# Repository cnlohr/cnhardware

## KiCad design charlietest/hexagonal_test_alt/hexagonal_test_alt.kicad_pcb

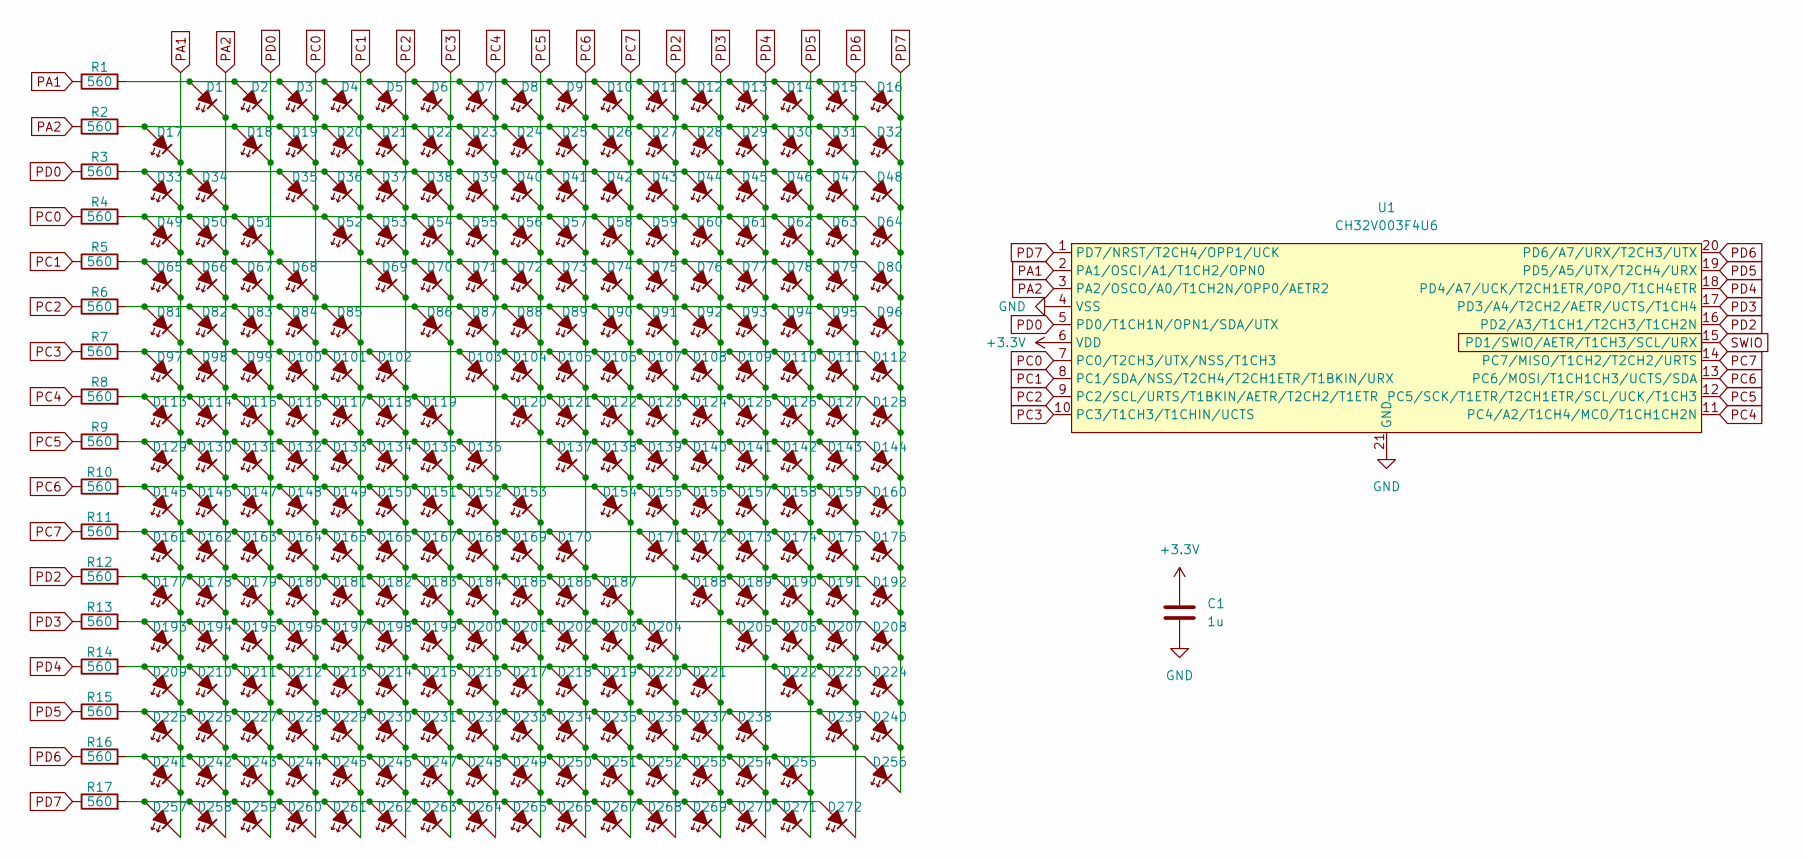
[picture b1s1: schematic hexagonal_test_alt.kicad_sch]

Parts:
C1: 1u; LCSC C52923
D1, D2, D3, D4, D5, D6, D7, D8, D9, D10, D11, D12, D13, D14, D15, D16, D17, D18, D19, D20, D21, D22, D23, D24, D25, D26, D27, D28, D29, D30, D31, D32, D33, D34, D35, D36, D37, D38, D39, D40, D41, D42, D43, D44, D45, D46, D47, D48, D49, D50, D51, D52, D53, D54, D55, D56, D57, D58, D59, D60, D61, D62, D63, D64, D65, D66, D67, D68, D69, D70, D71, D72, D73, D74, D75, D76, D77, D78, D79, D80, D81, D82, D83, D84, D85, D86, D87, D88, D89, D90, D91, D92, D93, D94, D95, D96, D97, D98, D99, D100, D101, D102, D103, D104, D105, D106, D107, D108, D109, D110, D111, D112, D113, D114, D115, D116, D117, D118, D119, D120, D121, D122, D123, D124, D125, D126, D127, D128, D129, D130, D131, D132, D133, D134, D135, D136, D137, D138, D139, D140, D141, D142, D143, D144, D145, D146, D147, D148, D149, D150, D151, D152, D153, D154, D155, D156, D157, D158, D159, D160, D161, D162, D163, D164, D165, D166, D167, D168, D169, D170, D171, D172, D173, D174, D175, D176, D177, D178, D179, D180, D181, D182, D183, D184, D185, D186, D187, D188, D189, D190, D191, D192, D193, D194, D195, D196, D197, D198, D199, D200, D201, D202, D203, D204, D205, D206, D207, D208, D209, D210, D211, D212, D213, D214, D215, D216, D217, D218, D219, D220, D221, D222, D223, D224, D225, D226, D227, D228, D229, D230, D231, D232, D233, D234, D235, D236, D237, D238, D239, D240, D241, D242, D243, D244, D245, D246, D247, D248, D249, D250, D251, D252, D253, D254, D255, D256, D257, D258, D259, D260, D261, D262, D263, D264, D265, D266, D267, D268, D269, D270, D271, D272: LED_45deg_Filled; LED_0603_1608Metric; LCSC C2290
R1, R2, R3, R4, R5, R6, R7, R8, R9, R10, R11, R12, R13, R14, R15, R16, R17: 560; R_0402_1005Metric_COMPACT; LCSC C17798
U1: CH32V003F4U6; QFN-20-1EP_3x3mm_P0.4mm_EP1.65x1.65mm; LCSC C5299908

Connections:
+3.3V: C1.1, U1.6 (VDD)
GND: C1.2, U1.4 (VSS), U1.21 (GND)
unnamed: D1.2 (A), D2.2 (A), D3.2 (A), D4.2 (A), D5.2 (A), D6.2 (A), D7.2 (A), D8.2 (A), D9.2 (A), D10.2 (A), D11.2 (A), D12.2 (A), D13.2 (A), D14.2 (A), D15.2 (A), D16.2 (A), R1.2
unnamed: D17.2 (A), D18.2 (A), D19.2 (A), D20.2 (A), D21.2 (A), D22.2 (A), D23.2 (A), D24.2 (A), D25.2 (A), D26.2 (A), D27.2 (A), D28.2 (A), D29.2 (A), D30.2 (A), D31.2 (A), D32.2 (A), R2.2
unnamed: D33.2 (A), D34.2 (A), D35.2 (A), D36.2 (A), D37.2 (A), D38.2 (A), D39.2 (A), D40.2 (A), D41.2 (A), D42.2 (A), D43.2 (A), D44.2 (A), D45.2 (A), D46.2 (A), D47.2 (A), D48.2 (A), R3.2
unnamed: D49.2 (A), D50.2 (A), D51.2 (A), D52.2 (A), D53.2 (A), D54.2 (A), D55.2 (A), D56.2 (A), D57.2 (A), D58.2 (A), D59.2 (A), D60.2 (A), D61.2 (A), D62.2 (A), D63.2 (A), D64.2 (A), R4.2
unnamed: D65.2 (A), D66.2 (A), D67.2 (A), D68.2 (A), D69.2 (A), D70.2 (A), D71.2 (A), D72.2 (A), D73.2 (A), D74.2 (A), D75.2 (A), D76.2 (A), D77.2 (A), D78.2 (A), D79.2 (A), D80.2 (A), R5.2
unnamed: D81.2 (A), D82.2 (A), D83.2 (A), D84.2 (A), D85.2 (A), D86.2 (A), D87.2 (A), D88.2 (A), D89.2 (A), D90.2 (A), D91.2 (A), D92.2 (A), D93.2 (A), D94.2 (A), D95.2 (A), D96.2 (A), R6.2
unnamed: D97.2 (A), D98.2 (A), D99.2 (A), D100.2 (A), D101.2 (A), D102.2 (A), D103.2 (A), D104.2 (A), D105.2 (A), D106.2 (A), D107.2 (A), D108.2 (A), D109.2 (A), D110.2 (A), D111.2 (A), D112.2 (A), R7.2
unnamed: D113.2 (A), D114.2 (A), D115.2 (A), D116.2 (A), D117.2 (A), D118.2 (A), D119.2 (A), D120.2 (A), D121.2 (A), D122.2 (A), D123.2 (A), D124.2 (A), D125.2 (A), D126.2 (A), D127.2 (A), D128.2 (A), R8.2
unnamed: D129.2 (A), D130.2 (A), D131.2 (A), D132.2 (A), D133.2 (A), D134.2 (A), D135.2 (A), D136.2 (A), D137.2 (A), D138.2 (A), D139.2 (A), D140.2 (A), D141.2 (A), D142.2 (A), D143.2 (A), D144.2 (A), R9.2
unnamed: D145.2 (A), D146.2 (A), D147.2 (A), D148.2 (A), D149.2 (A), D150.2 (A), D151.2 (A), D152.2 (A), D153.2 (A), D154.2 (A), D155.2 (A), D156.2 (A), D157.2 (A), D158.2 (A), D159.2 (A), D160.2 (A), R10.2
unnamed: D161.2 (A), D162.2 (A), D163.2 (A), D164.2 (A), D165.2 (A), D166.2 (A), D167.2 (A), D168.2 (A), D169.2 (A), D170.2 (A), D171.2 (A), D172.2 (A), D173.2 (A), D174.2 (A), D175.2 (A), D176.2 (A), R11.2
unnamed: D177.2 (A), D178.2 (A), D179.2 (A), D180.2 (A), D181.2 (A), D182.2 (A), D183.2 (A), D184.2 (A), D185.2 (A), D186.2 (A), D187.2 (A), D188.2 (A), D189.2 (A), D190.2 (A), D191.2 (A), D192.2 (A), R12.2
unnamed: D193.2 (A), D194.2 (A), D195.2 (A), D196.2 (A), D197.2 (A), D198.2 (A), D199.2 (A), D200.2 (A), D201.2 (A), D202.2 (A), D203.2 (A), D204.2 (A), D205.2 (A), D206.2 (A), D207.2 (A), D208.2 (A), R13.2
unnamed: D209.2 (A), D210.2 (A), D211.2 (A), D212.2 (A), D213.2 (A), D214.2 (A), D215.2 (A), D216.2 (A), D217.2 (A), D218.2 (A), D219.2 (A), D220.2 (A), D221.2 (A), D222.2 (A), D223.2 (A), D224.2 (A), R14.2
unnamed: D225.2 (A), D226.2 (A), D227.2 (A), D228.2 (A), D229.2 (A), D230.2 (A), D231.2 (A), D232.2 (A), D233.2 (A), D234.2 (A), D235.2 (A), D236.2 (A), D237.2 (A), D238.2 (A), D239.2 (A), D240.2 (A), R15.2
unnamed: D241.2 (A), D242.2 (A), D243.2 (A), D244.2 (A), D245.2 (A), D246.2 (A), D247.2 (A), D248.2 (A), D249.2 (A), D250.2 (A), D251.2 (A), D252.2 (A), D253.2 (A), D254.2 (A), D255.2 (A), D256.2 (A), R16.2
unnamed: D257.2 (A), D258.2 (A), D259.2 (A), D260.2 (A), D261.2 (A), D262.2 (A), D263.2 (A), D264.2 (A), D265.2 (A), D266.2 (A), D267.2 (A), D268.2 (A), D269.2 (A), D270.2 (A), D271.2 (A), D272.2 (A), R17.2
PA1: D17.1 (K), D33.1 (K), D49.1 (K), D65.1 (K), D81.1 (K), D97.1 (K), D113.1 (K), D129.1 (K), D145.1 (K), D161.1 (K), D177.1 (K), D193.1 (K), D209.1 (K), D225.1 (K), D241.1 (K), D257.1 (K), R1.1, U1.2 (PA1/OSCI/A1/T1CH2/OPN0)
PA2: D1.1 (K), D34.1 (K), D50.1 (K), D66.1 (K), D82.1 (K), D98.1 (K), D114.1 (K), D130.1 (K), D146.1 (K), D162.1 (K), D178.1 (K), D194.1 (K), D210.1 (K), D226.1 (K), D242.1 (K), D258.1 (K), R2.1, U1.3 (PA2/OSCO/A0/T1CH2N/OPP0/AETR2)
PC0: D3.1 (K), D19.1 (K), D35.1 (K), D68.1 (K), D84.1 (K), D100.1 (K), D116.1 (K), D132.1 (K), D148.1 (K), D164.1 (K), D180.1 (K), D196.1 (K), D212.1 (K), D228.1 (K), D244.1 (K), D260.1 (K), R4.1, U1.7 (PC0/T2CH3/UTX/NSS/T1CH3)
PC1: D4.1 (K), D20.1 (K), D36.1 (K), D52.1 (K), D85.1 (K), D101.1 (K), D117.1 (K), D133.1 (K), D149.1 (K), D165.1 (K), D181.1 (K), D197.1 (K), D213.1 (K), D229.1 (K), D245.1 (K), D261.1 (K), R5.1, U1.8 (PC1/SDA/NSS/T2CH4/T2CH1ETR/T1BKIN/URX)
PC2: D5.1 (K), D21.1 (K), D37.1 (K), D53.1 (K), D69.1 (K), D102.1 (K), D118.1 (K), D134.1 (K), D150.1 (K), D166.1 (K), D182.1 (K), D198.1 (K), D214.1 (K), D230.1 (K), D246.1 (K), D262.1 (K), R6.1, U1.9 (PC2/SCL/URTS/T1BKIN/AETR/T2CH2/T1ETR)
PC3: D6.1 (K), D22.1 (K), D38.1 (K), D54.1 (K), D70.1 (K), D86.1 (K), D119.1 (K), D135.1 (K), D151.1 (K), D167.1 (K), D183.1 (K), D199.1 (K), D215.1 (K), D231.1 (K), D247.1 (K), D263.1 (K), R7.1, U1.10 (PC3/T1CH3/T1CHIN/UCTS)
PC4: D7.1 (K), D23.1 (K), D39.1 (K), D55.1 (K), D71.1 (K), D87.1 (K), D103.1 (K), D136.1 (K), D152.1 (K), D168.1 (K), D184.1 (K), D200.1 (K), D216.1 (K), D232.1 (K), D248.1 (K), D264.1 (K), R8.1, U1.11 (PC4/A2/T1CH4/MCO/T1CH1CH2N)
PC5: D8.1 (K), D24.1 (K), D40.1 (K), D56.1 (K), D72.1 (K), D88.1 (K), D104.1 (K), D120.1 (K), D153.1 (K), D169.1 (K), D185.1 (K), D201.1 (K), D217.1 (K), D233.1 (K), D249.1 (K), D265.1 (K), R9.1, U1.12 (PC5/SCK/T1ETR/T2CH1ETR/SCL/UCK/T1CH3)
PC6: D9.1 (K), D25.1 (K), D41.1 (K), D57.1 (K), D73.1 (K), D89.1 (K), D105.1 (K), D121.1 (K), D137.1 (K), D170.1 (K), D186.1 (K), D202.1 (K), D218.1 (K), D234.1 (K), D250.1 (K), D266.1 (K), R10.1, U1.13 (PC6/MOSI/T1CH1CH3/UCTS/SDA)
PC7: D10.1 (K), D26.1 (K), D42.1 (K), D58.1 (K), D74.1 (K), D90.1 (K), D106.1 (K), D122.1 (K), D138.1 (K), D154.1 (K), D187.1 (K), D203.1 (K), D219.1 (K), D235.1 (K), D251.1 (K), D267.1 (K), R11.1, U1.14 (PC7/MISO/T1CH2/T2CH2/URTS)
PD0: D2.1 (K), D18.1 (K), D51.1 (K), D67.1 (K), D83.1 (K), D99.1 (K), D115.1 (K), D131.1 (K), D147.1 (K), D163.1 (K), D179.1 (K), D195.1 (K), D211.1 (K), D227.1 (K), D243.1 (K), D259.1 (K), R3.1, U1.5 (PD0/T1CH1N/OPN1/SDA/UTX)
PD2: D11.1 (K), D27.1 (K), D43.1 (K), D59.1 (K), D75.1 (K), D91.1 (K), D107.1 (K), D123.1 (K), D139.1 (K), D155.1 (K), D171.1 (K), D204.1 (K), D220.1 (K), D236.1 (K), D252.1 (K), D268.1 (K), R12.1, U1.16 (PD2/A3/T1CH1/T2CH3/T1CH2N)
PD3: D12.1 (K), D28.1 (K), D44.1 (K), D60.1 (K), D76.1 (K), D92.1 (K), D108.1 (K), D124.1 (K), D140.1 (K), D156.1 (K), D172.1 (K), D188.1 (K), D221.1 (K), D237.1 (K), D253.1 (K), D269.1 (K), R13.1, U1.17 (PD3/A4/T2CH2/AETR/UCTS/T1CH4)
PD4: D13.1 (K), D29.1 (K), D45.1 (K), D61.1 (K), D77.1 (K), D93.1 (K), D109.1 (K), D125.1 (K), D141.1 (K), D157.1 (K), D173.1 (K), D189.1 (K), D205.1 (K), D238.1 (K), D254.1 (K), D270.1 (K), R14.1, U1.18 (PD4/A7/UCK/T2CH1ETR/OPO/T1CH4ETR)
PD5: D14.1 (K), D30.1 (K), D46.1 (K), D62.1 (K), D78.1 (K), D94.1 (K), D110.1 (K), D126.1 (K), D142.1 (K), D158.1 (K), D174.1 (K), D190.1 (K), D206.1 (K), D222.1 (K), D255.1 (K), D271.1 (K), R15.1, U1.19 (PD5/A5/UTX/T2CH4/URX)
PD6: D15.1 (K), D31.1 (K), D47.1 (K), D63.1 (K), D79.1 (K), D95.1 (K), D111.1 (K), D127.1 (K), D143.1 (K), D159.1 (K), D175.1 (K), D191.1 (K), D207.1 (K), D223.1 (K), D239.1 (K), D272.1 (K), R16.1, U1.20 (PD6/A7/URX/T2CH3/UTX)
PD7: D16.1 (K), D32.1 (K), D48.1 (K), D64.1 (K), D80.1 (K), D96.1 (K), D112.1 (K), D128.1 (K), D144.1 (K), D160.1 (K), D176.1 (K), D192.1 (K), D208.1 (K), D224.1 (K), D240.1 (K), D256.1 (K), R17.1, U1.1 (PD7/NRST/T2CH4/OPP1/UCK)
SWIO: U1.15 (PD1/SWIO/AETR/T1CH3/SCL/URX)

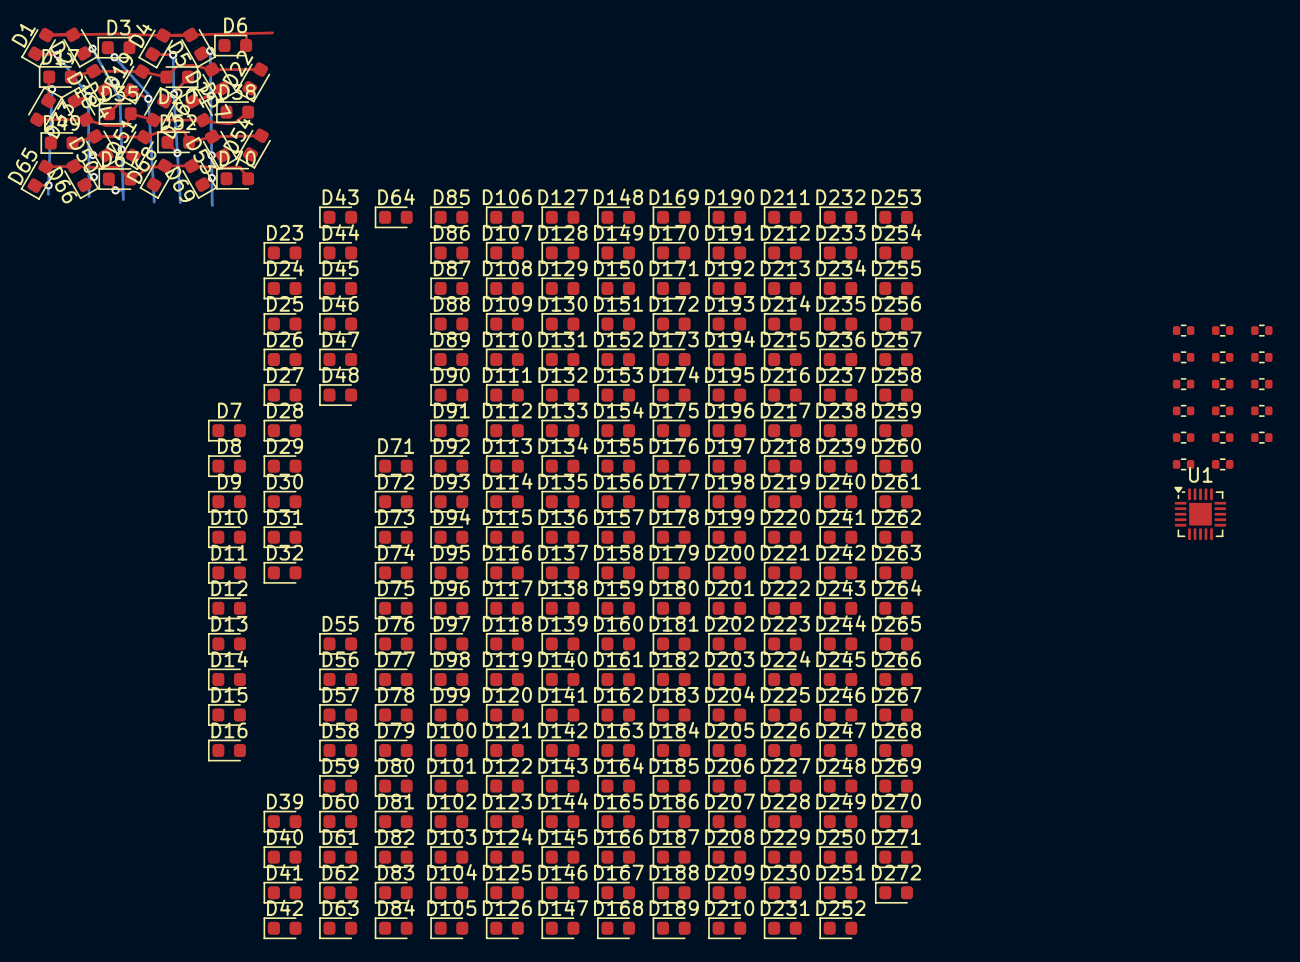
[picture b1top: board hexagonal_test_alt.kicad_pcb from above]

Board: 2 copper layers, 290 parts (0 on the bottom side), 35 nets.

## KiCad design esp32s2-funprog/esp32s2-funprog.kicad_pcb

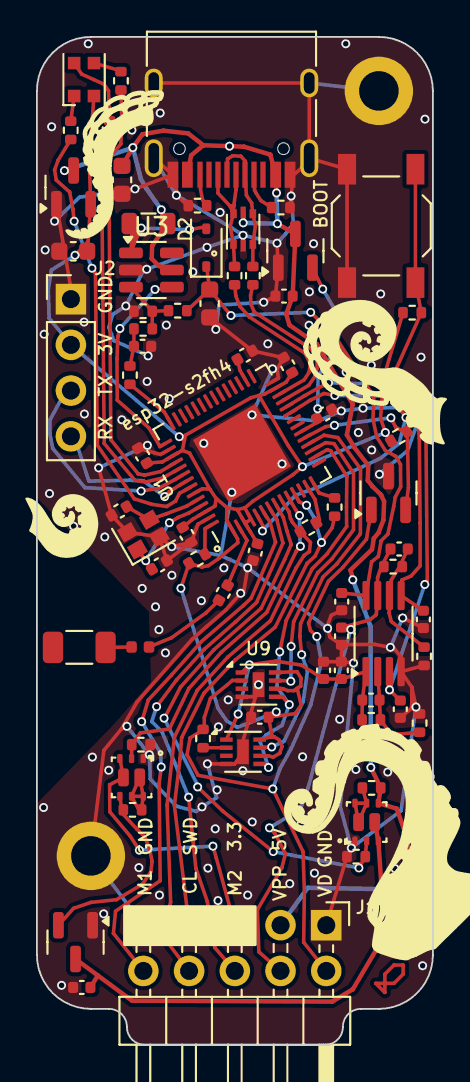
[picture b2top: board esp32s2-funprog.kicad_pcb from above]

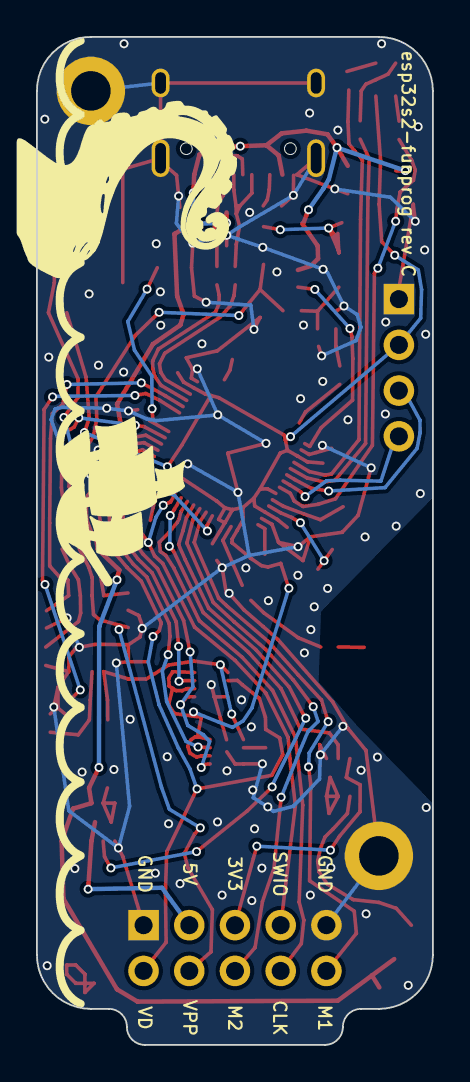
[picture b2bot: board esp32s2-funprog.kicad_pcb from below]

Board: 2 copper layers, 22.0 x 56.0 mm, 79 parts (2 on the bottom side), 57 nets.

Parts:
A1: ANT; R_1206_3216Metric
C1, C14, C15, C17, C21, C23, C24: 10p; C_0402_1005Metric
C2, C3: 2.2p; C_0402_1005Metric
C4, C5, C8, C9, C10, C11, C13, C16, C26: 1u; C_0402_1005Metric
C6, C12, C25: 10u; C_0603_1608Metric
C7, C18, C22: 100n; C_0402_1005Metric
D1: LED_RAGB; LED_WS2812B-2020_PLCC4_2.0x2.0mm
D2: 1N5819WS; D_SOD-323
D4: USBLC6-2P6-TVS; SOT-666
G1: artwork; Tentacle1-Astronautilus
G2: artwork; Tentacle2-Astronautilus
G3: artwork; BoatOnWaterLarge-Astronautilus
G4: artwork; Tentacle4-Astronautilus
G5: artwork; TentacleLargeFlip-Astronautilus
G6: artwork; TentacleLarge-Astronautilus
J1: OPGM; PinHeader_2x05_P2.54mm_Horizontal
J2: PGM; PinHeader_1x04_P2.54mm_Vertical
J3: USB_C_Receptacle_USB2.0; USB_C_Receptacle_HRO_TYPE-C-31-M-12
J4, J5: MOUNT; MountingHole_2.2mm_M2_DIN965_Pad
L1: 6.8nH; L_0402_1005Metric
L2: 4.7u500mA; L_0805_2012Metric
Q1, Q2: SE4625-PandN; DFN-6-2x2-SplitPad
Q4: 2N7002; SOT-23
R1, R2, R3, R4, R7, R8, R30: 10k; R_0402_1005Metric
R5, R6, R11, R12, R20, R22: 5.1k; R_0402_1005Metric
R9, R10: 22; R_0402_1005Metric
R13, R14, R15, R16: 510; R_0402_1005Metric
R17, R18, R24: 2.2k; R_0402_1005Metric
R19, R21: 15k; R_0402_1005Metric
R23: 12k; R_0402_1005Metric
SW1: TS-1187A-B-A-B; SW_SPST_TL3342
U1: ESP32-S2; ESP32S2
U2, U4, U6: XC6206P332; SOT-23
U3: MT3608; SOT-23-6
U5: COSNE5532; MSOP-8_3x3mm_P0.65mm
U9, U14: AT8837; DFN-8-1EP_2x2mm_P0.45mm_EP0.64x1.38mm
Y1: 40MHz; Crystal_SMD_2016-4Pin_2.0x1.6mm

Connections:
3V3SW: J1.5, Q1.3 (D2), Q1.8 (D2)
5VSW: J1.3, Q2.3 (D2), Q2.8 (D2)
+VSW: C7.1, C25.1, D2.1 (K), R23.2, U5.8 (Vcc)
BOOSTEN: U1.43 (MTCK), U3.4 (EN)
BOOSTV: R24.2, U1.42 (GPIO38)
CHIP_PU: R6.1, U1.56 (CHIP_PU)
D+: D4.1 (IO1), D4.6 (IO1), J3.A6 (D+), J3.B6 (D+), R10.2
D-: D4.3 (IO2), D4.4 (IO2), J3.A7 (D-), J3.B7 (D-), R9.1
DAC1: C14.2, U1.23 (DAC1), U5.3 (I1+)
DAC2: C15.2, U1.24 (DAC2), U5.5 (I2+)
GND: C2.1, C3.1, C4.2, C5.2, C6.2, C7.2, C8.2, C9.2, C10.1, C11.2, C12.2, C13.2, C14.1, C15.1, C16.2, C18.2, C22.2, C23.2, C24.2, C25.2, C26.1, D4.2 (GND), J1.1, J1.9, J2.1, J3.A1 (GND), J3.A12 (GND), J3.B1 (GND), J3.B12 (GND), J3.S1 (SHIELD), J4.1, J5.1, Q1.1 (S1), Q2.1 (S1), Q4.3 (S), R3.1, R4.1, R11.2, R12.2, R16.1, R20.1, R22.1, SW1.1 (A), U1.28 (GPIO21), U1.44 (MTDO0), U1.55 (GPIO46), U1.57 (GND), U2.1 (GND), U3.2 (GND), U4.1 (GND), U5.4 (GND), U6.1 (GND), U9.4 (GND), U9.9 (FLAG), U14.4 (GND), U14.9 (FLAG), Y1.2, Y1.4
GPIO0: R5.2, SW1.2 (B), U1.5 (GPIO0)
MULTI1: J1.10, U1.6 (GPIO1)
MULTI2: J1.6, U1.7 (GPIO2)
unnamed: A1.1, L1.1
unnamed: C1.1, L1.2
unnamed: C18.1, R17.1, R24.1
unnamed: D1.4 (BK), R15.2
unnamed: D1.3 (GK), R14.2
unnamed: D1.1 (RK), R13.2
unnamed: D2.2 (A), L2.2, U3.1 (SW)
unnamed: J3.A5 (CC1), R11.1
unnamed: J3.B5 (CC2), R12.1
unnamed: Q1.5 (G2), Q1.6 (D1), Q1.7 (D1), R7.2
unnamed: Q1.4 (S2), R7.1, U6.2 (Q)
unnamed: Q2.5 (G2), Q2.6 (D1), Q2.7 (D1), R8.2
unnamed: R9.2, U1.25 (GPIO19)
unnamed: R10.1, U1.26 (GPIO20)
unnamed: R13.1, U1.50 (GPIO45)
unnamed: C1.2, U1.2 (LNA_IN)
unnamed: R14.1, U1.46 (MTDI)
unnamed: R15.1, U1.47 (MTMS)
unnamed: C4.1, U1.30 (VDD_SPI)
unnamed: C3.2, U1.52 (XTAL_N), Y1.3
unnamed: C2.2, U1.53 (XTAL_P), Y1.1
unnamed: R16.2, R17.2, R23.1, U3.3 (FB)
unnamed: R30.1, U14.2 (OUT1)
OD1: U1.16 (GPIO11), U9.5 (IN2), U14.5 (IN2)
OEN1: U1.17 (GPIO12), U9.7 (nSLP)
OPEN1: U1.18 (GPIO13), U14.7 (nSLP)
RX: J2.4, U1.49 (U0XD)
SWCL: J1.8, R1.1, U1.9 (GPIO4)
SWIO: J1.7, R2.1, U1.11 (GPIO6)
SWPUC: R1.2, U1.13 (GPIO8)
SWPUD: R2.2, U1.14 (GPIO9)
TX: J2.3, U1.48 (U0TXD)
V1FB: C17.2, R19.1, R20.2, U5.2 (I1-)
V2FB: C21.2, R21.1, R22.2, U5.6 (I2-)
VBUS: C10.2, C12.1, C26.2, D4.5 (VB), J3.A4 (VBUS), J3.A9 (VBUS), J3.B4 (VBUS), J3.B9 (VBUS), L2.1, Q2.4 (S2), R8.1, U2.3 (I), U3.5 (IN), U4.3 (I), U6.3 (I)
VCCCTL3: Q1.2 (G1), R3.2, U1.10 (GPIO5)
VCCCTL5: Q2.2 (G1), R4.2, U1.8 (GPIO3)
VD1: C17.1, C22.1, C24.1, R19.2, U5.1 (O1), U9.1 (VM), U14.1 (VM)
VD2: C21.1, C23.1, J1.4, R21.2, U5.7 (O2)
VDD: C5.1, C6.1, C8.1, C9.1, C11.1, C13.1, D1.2 (A), J2.2, R5.1, R6.2, R18.1, U1.1 (VDDA), U1.3 (VDD3P3), U1.4 (VDD3P3), U1.27 (VDD3P3_RTC_IO), U1.45 (VDD3P3_CPU), U1.51 (VDDA), U1.54 (VDDA), U4.2 (Q), U9.6 (IN1), U9.8 (VCC), U14.6 (IN1), U14.8 (VCC)
VDDA: C16.1, U1.20 (V333P3_RTC), U2.2 (Q)
VPI1: Q4.2 (D), R18.2, U1.19 (GPIO14)
VPP1: J1.2, Q4.1 (G), R30.2, U9.2 (OUT1)

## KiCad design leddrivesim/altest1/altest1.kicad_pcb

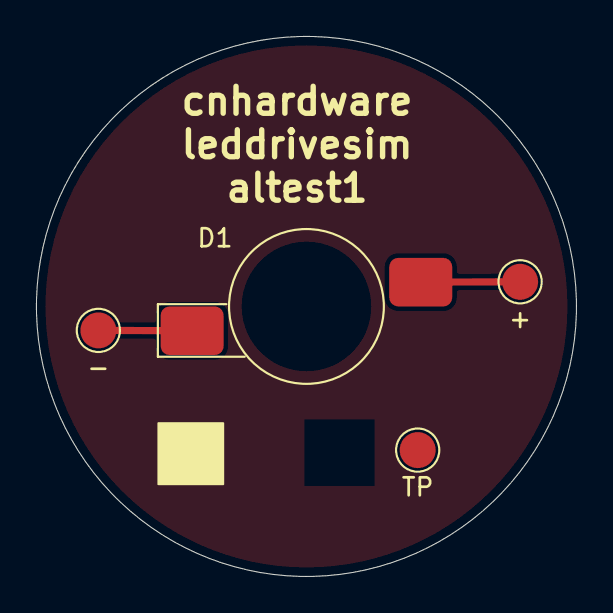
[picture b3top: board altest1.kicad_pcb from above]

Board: 2 copper layers, 30.0 x 30.0 mm, 4 parts (0 on the bottom side), 2 nets.

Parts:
D1: LED_1W_3W; LED_1W_3W_R8-FOR-ALUMINIUM-SUBSTRATE
TP1: +; TestPoint_Pad_D2.0mm
TP2: -; TestPoint_Pad_D2.0mm
TP3: TP; TestPoint_Pad_D2.0mm

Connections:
unnamed: D1.2 (A), TP1.1
unnamed: D1.1 (K), TP2.1

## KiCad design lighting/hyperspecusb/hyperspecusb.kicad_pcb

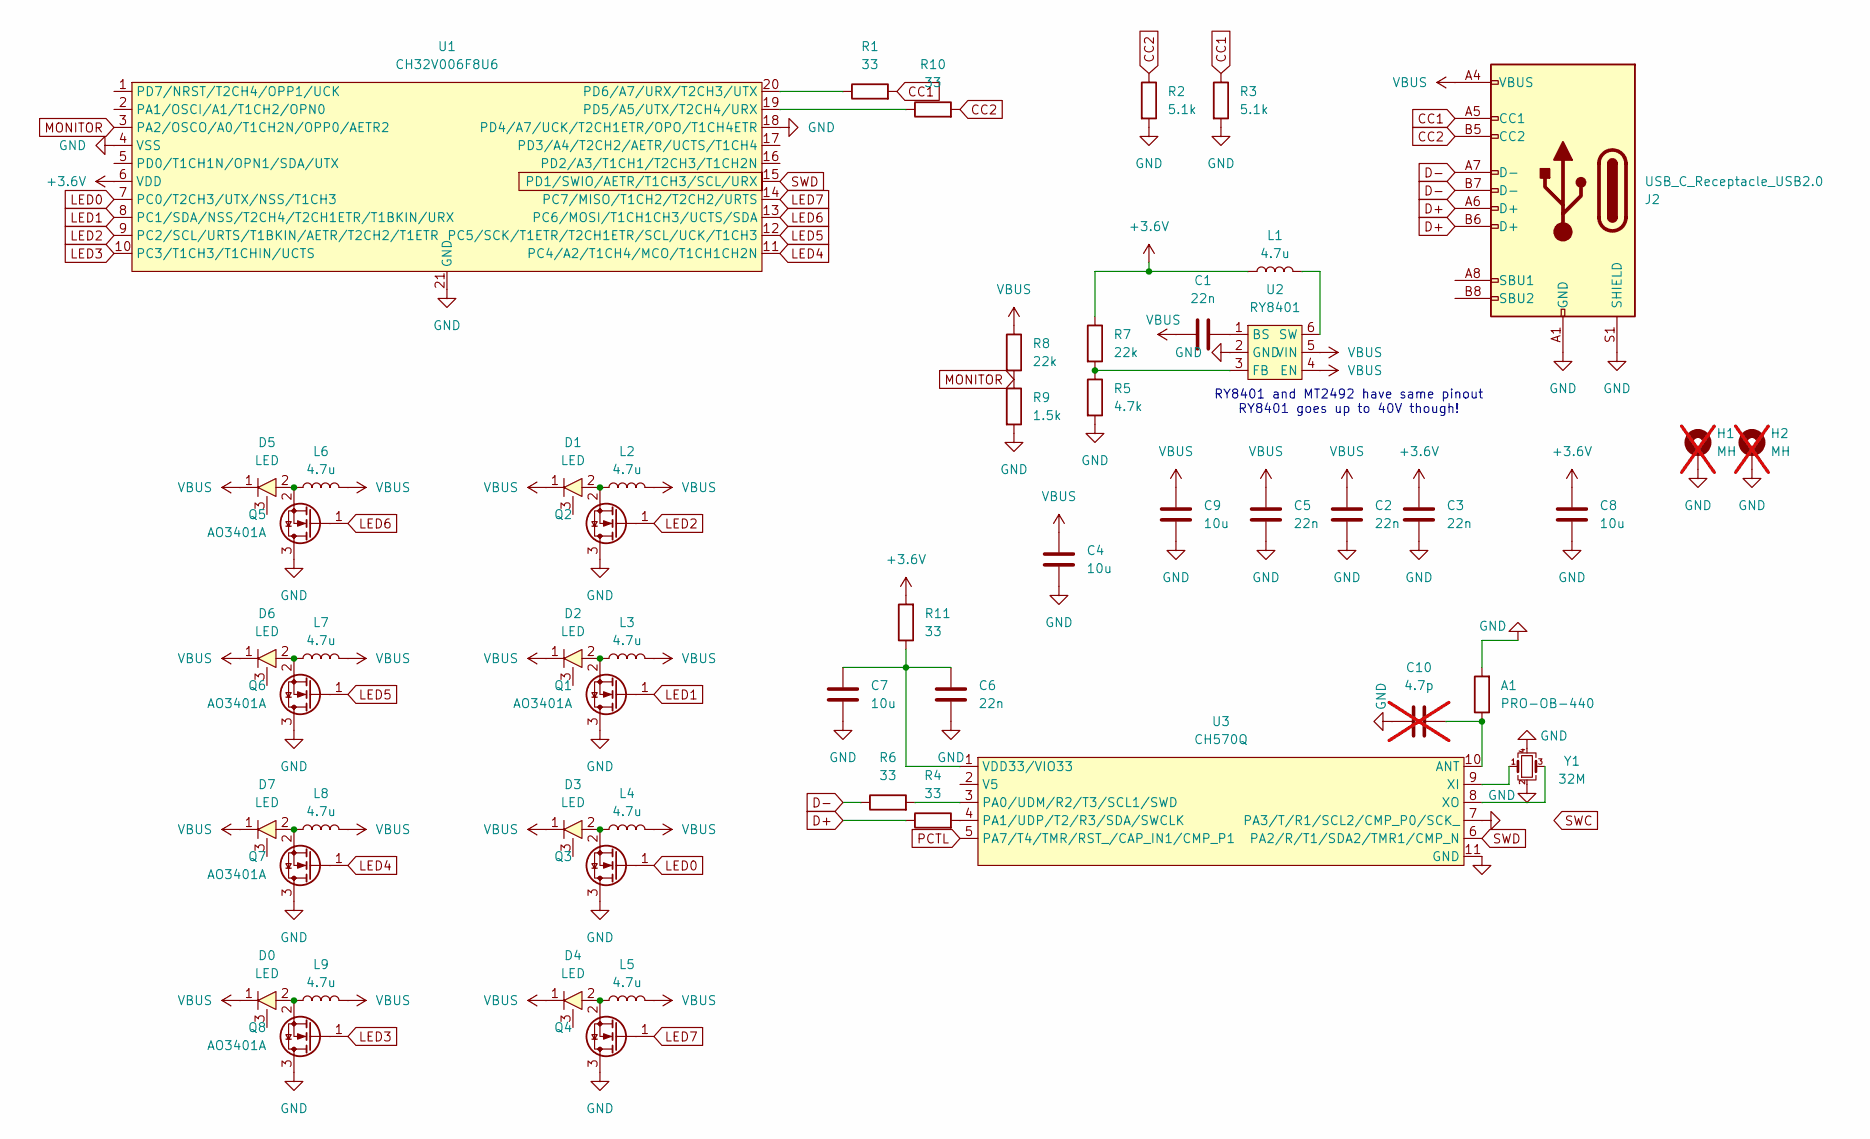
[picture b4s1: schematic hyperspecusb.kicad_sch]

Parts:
A1: PRO-OB-440; Abracon_PRO-OB-440; LCSC C5122736
C1, C2, C3, C5, C6: 22n; C_0402_1005Metric; LCSC C1532
C4, C7, C8, C9: 10u; C_0805_2012Metric; LCSC C15850
C10: 4.7p; C_0402_1005Metric; not fitted
D0, D1, D2, D3, D4, D5, D6, D7: LED; LED_3535_3W_W_PAD
H1, H2: MH; MountingHole_3.2mm_M3_ISO7380_Pad; not fitted
J2: USB_C_Receptacle_USB2.0; USB_C_SMT_ONLY_Receptacle_USB2.0; LCSC C2927040
L1, L2, L3, L4, L5, L6, L7, L8, L9: 4.7u; L_1008_2520Metric; LCSC C88528
Q1, Q2, Q3, Q4, Q5, Q6, Q7, Q8: AO3401A; SOT-23; LCSC C15127
R1, R4, R6, R10, R11: 33; R_0603_1608Metric; LCSC C23140
R2, R3: 5.1k; R_0402_1005Metric; LCSC C25905
R5: 4.7k; R_0402_1005Metric; LCSC C25900
R7, R8: 22k; R_0603_1608Metric; LCSC C31850
R9: 1.5k; R_0402_1005Metric; LCSC C25867
U1: CH32V006F8U6; QFN-20-1EP_3x3mm_P0.4mm_EP1.65x1.65mm; LCSC C42431288
U2: RY8401; SOT-23-6; LCSC C2912960
U3: CH570Q; DFN-10-1EP_3x3mm_P0.5mm_EP1.7x2.5mm; LCSC C49260680
Y1: 32M; Crystal_SMD_2016-4Pin_2.0x1.6mm; LCSC C718072

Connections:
+3.6V: C3.2, C8.2, L1.1, R7.1, R11.2, U1.6 (VDD)
CC1: J2.A5 (CC1), R1.2, R3.1
CC2: J2.B5 (CC2), R2.1, R10.2
D+: J2.A6 (D+), J2.B6 (D+), R4.1
D-: J2.A7 (D-), J2.B7 (D-), R6.1
GND: A1.2, C2.1, C3.1, C4.1, C5.1, C6.1, C7.1, C8.1, C9.1, C10.2, H1.1, H2.1, J2.A1 (GND), J2.A12 (GND), J2.B1 (GND), J2.B12 (GND), J2.S1 (SHIELD), Q1.3 (D), Q2.3 (D), Q3.3 (D), Q4.3 (D), Q5.3 (D), Q6.3 (D), Q7.3 (D), Q8.3 (D), R2.2, R3.2, R5.2, R9.2, U1.4 (VSS), U1.18 (PD4/A7/UCK/T2CH1ETR/OPO/T1CH4ETR), U1.21 (GND), U2.2 (GND), U3.7 (PA3/T/R1/SCL2/CMP_P0/SCK_), U3.11 (GND), Y1.2, Y1.4
LED0: Q3.1 (G), U1.7 (PC0/T2CH3/UTX/NSS/T1CH3)
LED1: Q1.1 (G), U1.8 (PC1/SDA/NSS/T2CH4/T2CH1ETR/T1BKIN/URX)
LED2: Q2.1 (G), U1.9 (PC2/SCL/URTS/T1BKIN/AETR/T2CH2/T1ETR)
LED3: Q8.1 (G), U1.10 (PC3/T1CH3/T1CHIN/UCTS)
LED4: Q7.1 (G), U1.11 (PC4/A2/T1CH4/MCO/T1CH1CH2N)
LED5: Q6.1 (G), U1.12 (PC5/SCK/T1ETR/T2CH1ETR/SCL/UCK/T1CH3)
LED6: Q5.1 (G), U1.13 (PC6/MOSI/T1CH1CH3/UCTS/SDA)
LED7: Q4.1 (G), U1.14 (PC7/MISO/T1CH2/T2CH2/URTS)
MONITOR: R8.2, R9.1, U1.3 (PA2/OSCO/A0/T1CH2N/OPP0/AETR2)
unnamed: D2.2, L3.1, Q1.2 (S)
unnamed: D1.2, L2.1, Q2.2 (S)
unnamed: D3.2, L4.1, Q3.2 (S)
unnamed: D4.2, L5.1, Q4.2 (S)
unnamed: D5.2, L6.1, Q5.2 (S)
unnamed: D6.2, L7.1, Q6.2 (S)
unnamed: D7.2, L8.1, Q7.2 (S)
unnamed: D0.2, L9.1, Q8.2 (S)
unnamed: R10.1, U1.19 (PD5/A5/UTX/T2CH4/URX)
unnamed: R1.1, U1.20 (PD6/A7/URX/T2CH3/UTX)
unnamed: C1.2, U2.1 (BS)
unnamed: R5.1, R7.2, U2.3 (FB)
unnamed: L1.2, U2.6 (SW)
unnamed: A1.1, C10.1, U3.10 (ANT)
unnamed: R6.2, U3.3 (PA0/UDM/R2/T3/SCL1/SWD)
unnamed: R4.2, U3.4 (PA1/UDP/T2/R3/SDA/SWCLK)
unnamed: C6.2, C7.2, R11.1, U3.1 (VDD33/VIO33)
unnamed: U3.9 (XI), Y1.1
unnamed: U3.8 (XO), Y1.3
PCTL: U3.5 (PA7/T4/TMR/RST_/CAP_IN1/CMP_P1)
SWD: U1.15 (PD1/SWIO/AETR/T1CH3/SCL/URX), U3.6 (PA2/R/T1/SDA2/TMR1/CMP_N)
VBUS: C1.1, C2.2, C4.2, C5.2, C9.2, D0.1, D1.1, D2.1, D3.1, D4.1, D5.1, D6.1, D7.1, J2.A4 (VBUS), J2.A9 (VBUS), J2.B4 (VBUS), J2.B9 (VBUS), L2.2, L3.2, L4.2, L5.2, L6.2, L7.2, L8.2, L9.2, R8.1, U2.4 (EN), U2.5 (VIN)

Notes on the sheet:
RY8401 and MT2492 have same pinout RY8401 goes up to 40V though!

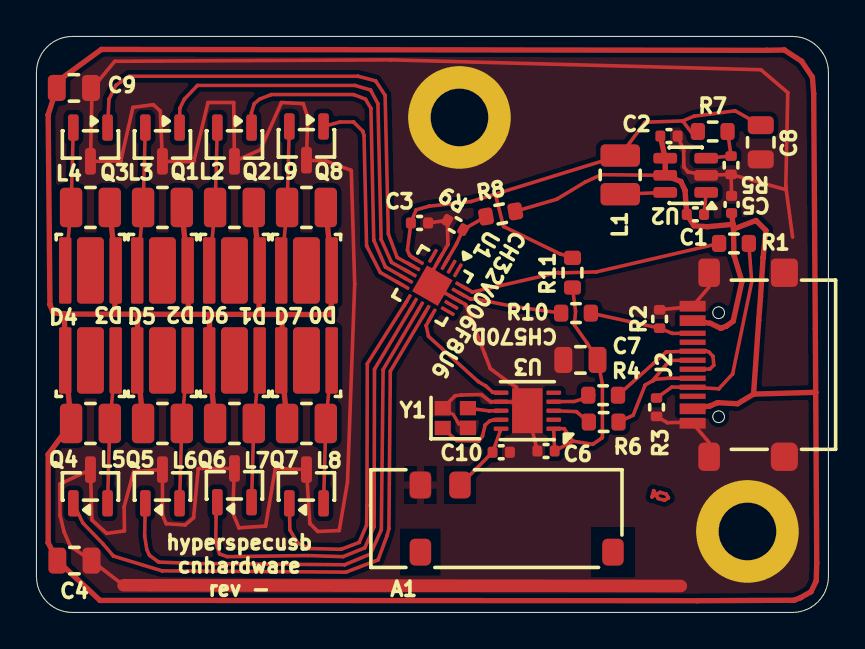
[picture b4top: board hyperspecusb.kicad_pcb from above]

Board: 2 copper layers, 44.0 x 32.0 mm, 54 parts (0 on the bottom side), 36 nets.
